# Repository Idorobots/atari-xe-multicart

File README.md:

# XE Multicart

A multi-game cartridge for the Atari 400/800/XL/XE with software game selection which can hold up to 127 games!

# How it works?

A `74HCT373` latch is used for extra address pins, it's accessed by writing to the cartridge control block (`$DF00`) causing a bank switch. After selecting appropriate ROM bank, the firmare resets the console in turn starting the game. To select another game, reboot your Atari.

# Assembly instructions
## PCB
Assuming that you already have the PCBs on hand, either by ordering them on-line or creating them yourself, the assembly is pretty simple - just solder the `74HTC373` latch, the transistor and the passive components. It is highly recommended to solder a socket for the memory chip as it makes it much easier to re-program it. **Also, keep in mind that the component side goes into the console facing down, so prepare your case accordingly.**

## Memory chip configuration

The PCB layout of this cartridge is customizable - you can fit any 28/32-pin JEDEC-compliant EPROM chip in the `27C` line or compatible flash memory chip with size ranging from as low as 64 kbit up to 8 mbit. Fitting larger chips means you will be able to store more game ROMs (up to 127 total), but you can also use this layout without the game selection firmware to store any single standard 8k/16k game you want.

### Jumper settings

There are four jumpers on the PCB - `JP1` to `JP4` - oriented vertically when looking at the top layer with the edge connector facing down:

```
      0   0   0   0\ UP
DOWN /0   0   0   0/
     \0   0   0   0
     JP1 JP2 JP3 JP4
```

These are used to configure the cartridge for the appropriate memory chip. The following table lists jumper settings for various common configurations (UP means "short top two pins", DOWN means "short bottom two pins" and X means "don't care"):

| Memory chip size | JP1  | JP2  | JP3  | JP4  |
| ---------------- | ---- | ---- | ---- | ---- |
| 64k (27C64)      | X    | X    | UP   | UP   |
| 128k (27C128)    | X    | X    | UP   | UP   |
| 256k (27C256)    | X    | X    | UP   | DOWN |
| 512k (27C512)    | X    | X    | UP   | DOWN |
| 1m (27C010)       | UP   | UP   | X    | DOWN |
| 2m (27C020)       | UP   | UP   | DOWN | DOWN |
| 4m (27C040)       | UP   | DOWN | DOWN | DOWN |
| 8m (27C080)       | DOWN | DOWN | DOWN | DOWN |

## Building the firmware
### Prerequisites
To succesfully build the firmware for the multicart, you will need to set up the following dependencies on your system:
- `make` - the Make build system,
- `python3` - Python programming language version 3.*,
- `gcc` - GNU Compiler Collection,
- `cc65`- the [CC65 compiler](https://cc65.github.io/).

### Build
In order to build the firmware & a cartridge image you will need some standard 8k/16k ROM files (obtainable freely on the Internet). Install all the dependencies, put your ROMs into the `roms/` directory and type:

```
make
```

This will run a script that automatically detects and arranges the games, builds the firmware and compiles a cartridge image ready for burning with your favourite EPROM burner.

Alternatively, you can supply a custom ROMs directory like this:

```
make ROMS=path/to/roms/directory
```

If you encounter any troubles while building, make sure to rebuild everything cleanly:

```
make clean && make
```
## Building from a docker container

In order to build the container itself run the following command in project directory

```
docker build -t atari_xe_multicart:latest .
```

After the container is ready to use run the following command to create `cart.bin` file. It assumes that .rom files are inside the /roms directory inside project directory.

```
docker run -ti --rm -v $(pwd)/roms/:/input/ -v $(pwd):/output/ atari_xe_multicart
```

# Running in an emulator

Multicart images don't work in any emulators that I know of, because they are using a custom (if simplistic) bank-switching mechanism. For testing purposes, you can run just the `menu.bin` (the game selection firmware) by loading it as a standard 8k cartridge ROM in your favourite Atari 800/XE emulator. For example:

```
atari800 -xl -xlxe_rom path/to/ATARIXL.ROM -cart menu.bin
```

It'll display the game selection menu, but any attempts at selecting a game will result in restarting the game selection menu.

# License

Software & hardware licensed under the MIT license (see LICENSE file for details). The OSHW logo comes from the [BFL library](http://www.baconfatlabs.com/2011/11/oshw-eagle-symbols-for-schematic-and-silkscreen/), licensed under CC-BY-SA. Any commercial product names seen on software screenshots are for demonstration purposes only and are not included with this product.

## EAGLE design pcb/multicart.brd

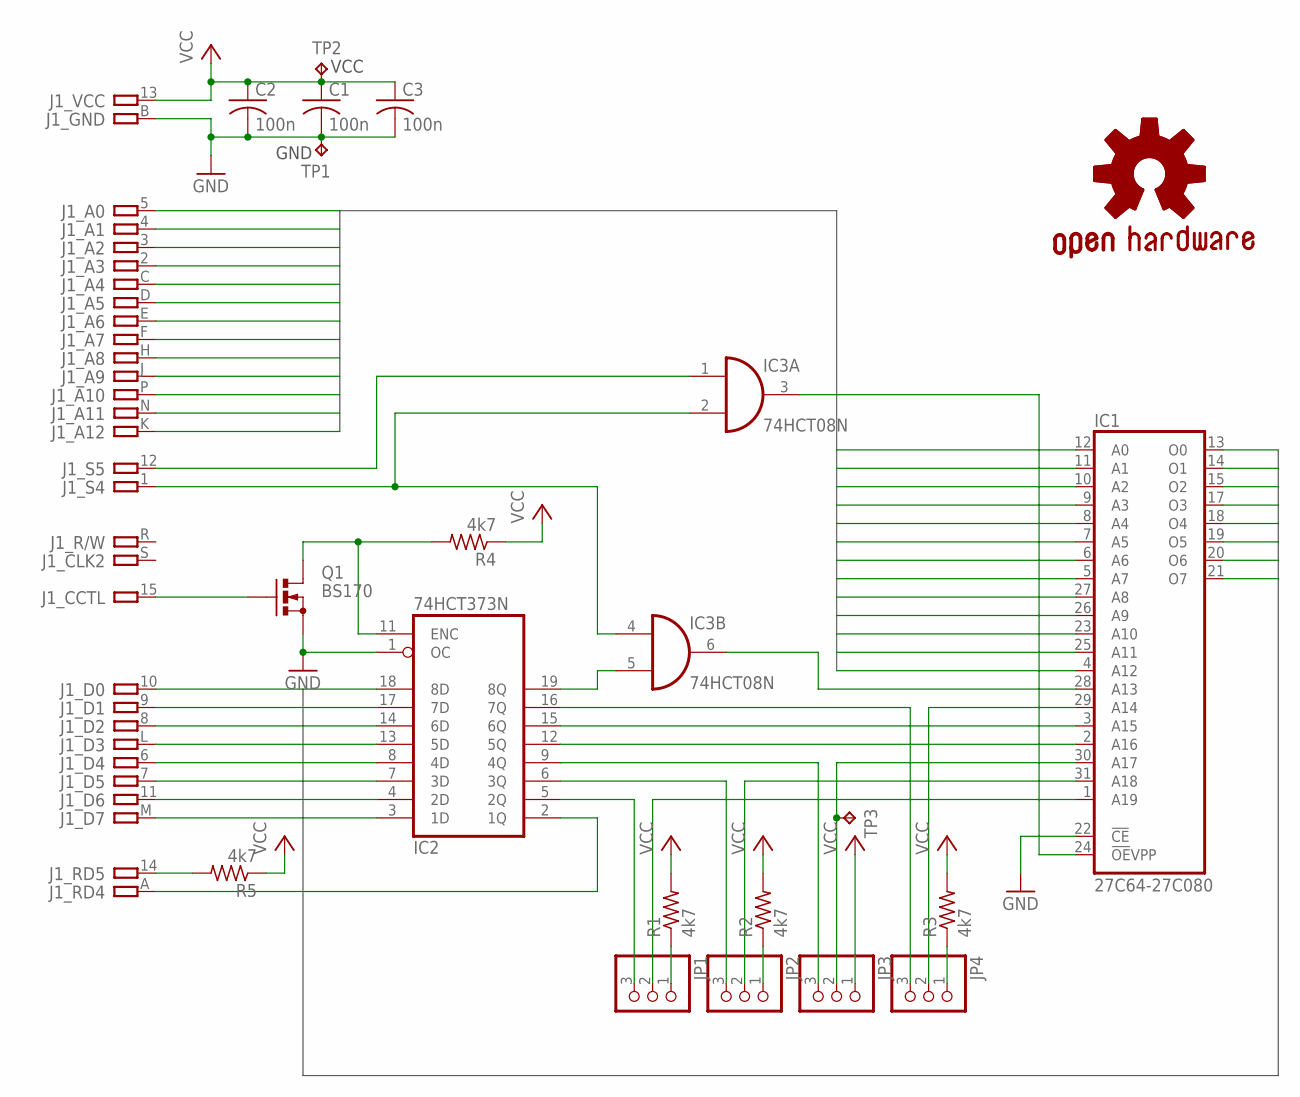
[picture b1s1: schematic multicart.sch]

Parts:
C1, C2, C3: 100n; C025-025X050
GOLD_ORB_SM1: OSHWLOGO_GOLD_ORB_SM; OSHW2
IC1: 27C64-27C080; DIL32
IC2: 74HCT373N; DIL20
IC3: 74HCT08N; DIL14
J1: ATARI-800
JP1, JP2, JP3, JP4: PINHD-1X3; 1X03
Q1: BS170; SOT54E
R1, R2, R3, R4, R5: 4k7; 0204/7
TP1, TP2, TP3: TPB1,27; B1,27

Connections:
A0: IC1.12 (A0), J1.5
A1: IC1.11 (A1), J1.4
A2: IC1.10 (A2), J1.3
A3: IC1.9 (A3), J1.2
A4: IC1.8 (A4), J1.C
A5: IC1.7 (A5), J1.D
A6: IC1.6 (A6), J1.E
A7: IC1.5 (A7), J1.F
A8: IC1.27 (A8), J1.H
A9: IC1.26 (A9), J1.J
A10: IC1.23 (A10), J1.P
A11: IC1.25 (A11), J1.N
A12: IC1.4 (A12), J1.K
D0: IC1.13 (O0), IC2.18 (8D), J1.10
D1: IC1.14 (O1), IC2.17 (7D), J1.9
D2: IC1.15 (O2), IC2.14 (6D), J1.8
D3: IC1.17 (O3), IC2.13 (5D), J1.L
D4: IC1.18 (O4), IC2.8 (4D), J1.6
D5: IC1.19 (O5), IC2.7 (3D), J1.7
D6: IC1.20 (O6), IC2.4 (2D), J1.11
D7: IC1.21 (O7), IC2.3 (1D), J1.M
GND: C1.2, C2.2, C3.2, IC1.16 (GND), IC1.22 (!CE), IC2.1 (OC), IC2.10 (GND), IC3.7 (GND), J1.B, Q1.S, TP1.TP
unnamed: IC2.19 (8Q), IC3.5 (I1)
unnamed: IC2.16 (7Q), JP4.3
unnamed: IC1.3 (A15), IC2.15 (6Q)
unnamed: IC1.2 (A16), IC2.12 (5Q)
unnamed: IC2.9 (4Q), JP3.3
unnamed: IC2.6 (3Q), JP2.3
unnamed: IC2.11 (ENC), Q1.D, R4.2
unnamed: J1.15, Q1.G
unnamed: JP1.1, R1.1
unnamed: IC1.31 (A18), JP2.2
unnamed: JP2.1, R2.1
unnamed: IC1.30 (A17), JP3.2, TP3.TP
unnamed: IC1.1 (A19), JP1.2
unnamed: IC2.5 (2Q), JP1.3
unnamed: IC1.29 (A14), JP4.2
unnamed: JP4.1, R3.1
unnamed: J1.14, R5.2
unnamed: IC3.1 (I0), J1.12
unnamed: IC3.2 (I1), IC3.4 (I0), J1.1
unnamed: IC1.28 (A13), IC3.6 (O)
unnamed: IC2.2 (1Q), J1.A
unnamed: IC1.24 (!OE!VPP), IC3.3 (O)
VCC: C1.1, C2.1, C3.1, IC1.32 (VCC), IC2.20 (VCC), IC3.14 (VCC), J1.13, JP3.1, R1.2, R2.2, R3.2, R4.1, R5.1, TP2.TP

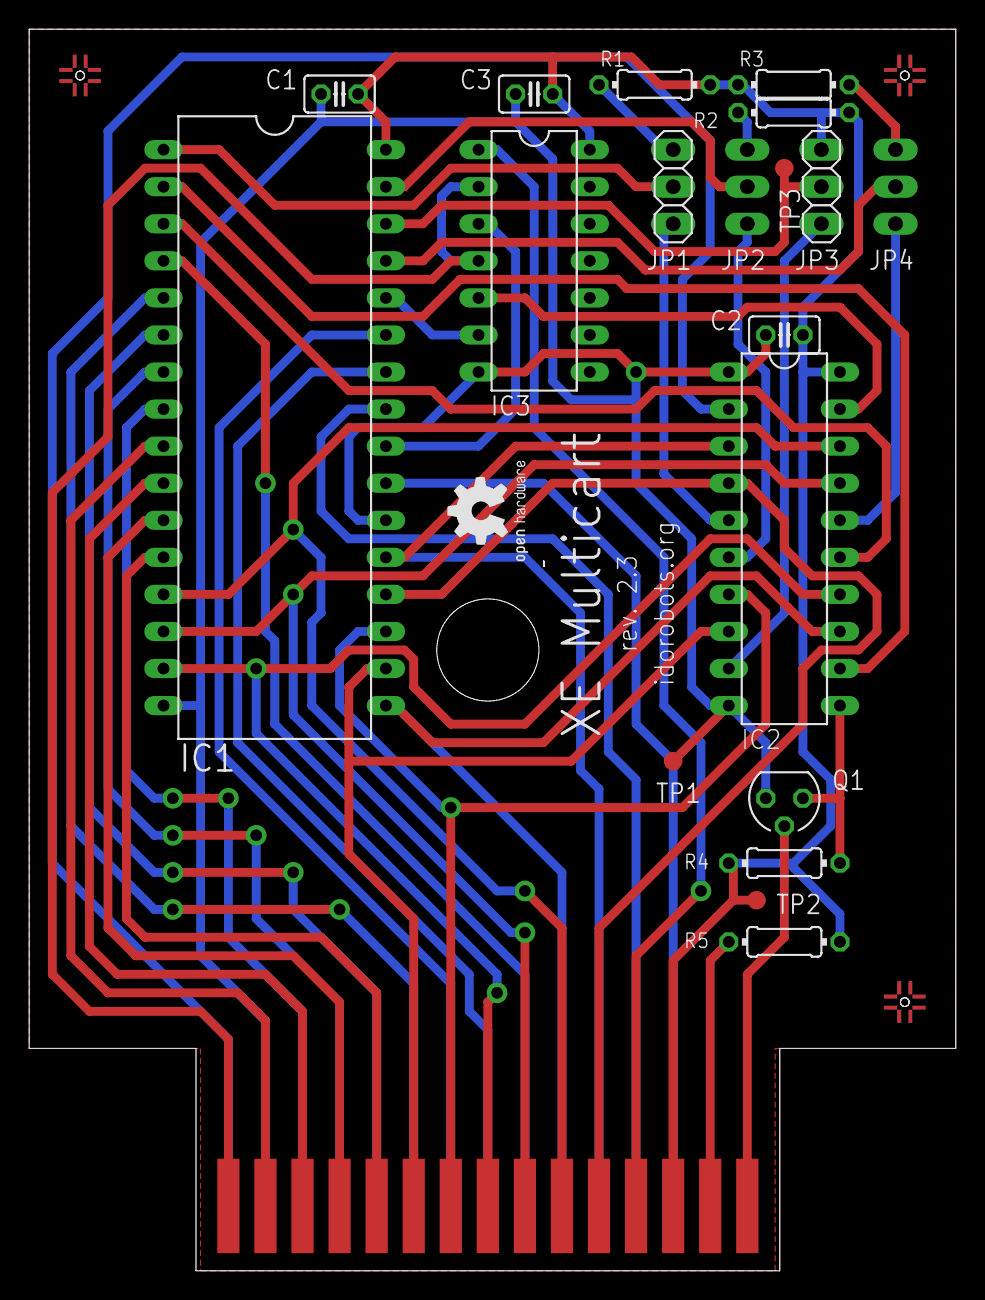
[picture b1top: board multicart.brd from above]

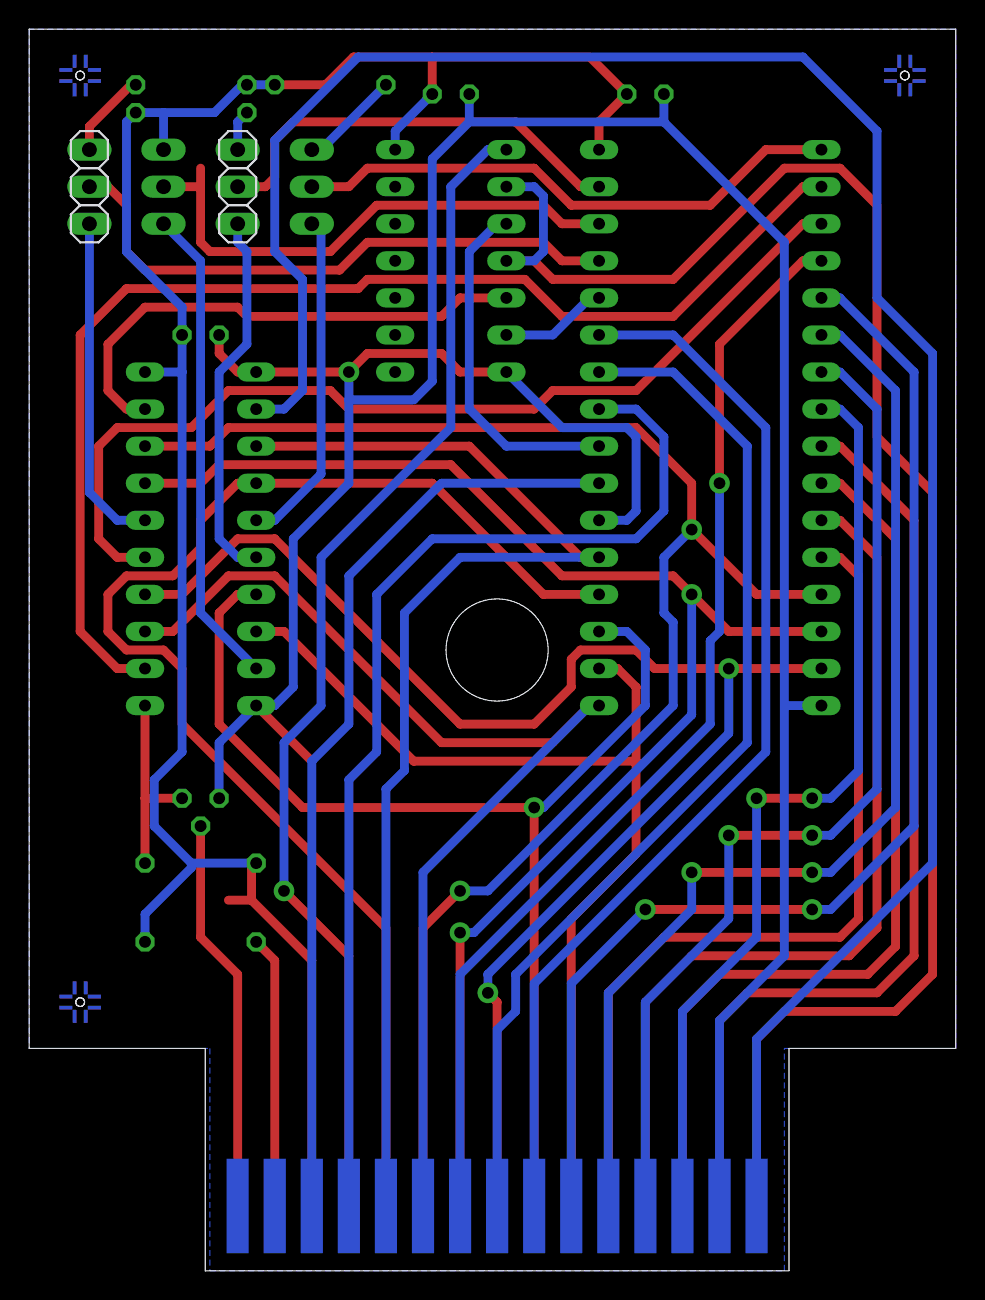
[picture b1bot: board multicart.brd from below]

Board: 2 copper layers, 63.5 x 85.1 mm, 27 parts (5 on the bottom side), 45 nets.

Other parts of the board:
U$1, U$2, U$3, U$4, U$5, U$6: PASSER-HOLE

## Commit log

2016-04-04 Added schematic of the multi-cart.
2016-04-04 Updated the README.
2016-04-04 Changed cart connector package & removed unused signals.
2016-04-04 Added PCB layout of the multicart.
2016-04-04 Added a stub of the game selection software.
2016-04-05 Swapped cart bank mapping & reorganized the PCB.
    Fixes #1
2016-04-05 Optimized the design.
2016-04-05 Added bypass caps to the design.
2016-04-06 Modified the design to support both 8k and 16k standard games.
2016-04-06 Implemented bulk of the firmware logic.
2016-04-06 Hold on... What if a game actually uses the second cart bank?
    Silly me.
2016-04-06 Ensured that the backed up code works as expected.
2016-04-06 Fixed bad C runtime teardown when swapping games.
    Fixes #4
2016-04-06 Refactored the code a little.
2016-04-07 Removed the RD5 line resistor.
2016-04-07 Optimized the design a little.
2016-04-07 Added pull-downs to the CCTL & R/W lines.
2016-04-08 Optimized the design by using AND gates.
2016-04-09 Moved some definitions into a header file.
2016-04-09 Added a better game selection menu.
2016-04-09 Moved Makefile outside of the src directory.
2016-04-09 Added a stub of cart creating script.
2016-04-09 Added cart.bin generation to the script.
2016-04-10 Improved game ordering in the selection menu.
2016-04-10 Fixed wonky if condition.
2016-04-10 Improved game selection screen.
2016-04-10 Updated the schematic to support 8-mbit flash chips.
2016-04-10 Updated the PCB design.
2016-04-10 Optimized the PCB design.
2016-04-10 Made firmware properly work with 8mbit flash.
2016-04-12 Added some sparkles to the PCB layout.
2016-04-12 Added OSHW logo to the PCB & the schematic.
2016-04-12 Updated the licensing info.
2016-04-13 Ensure that Python v3 is used when building the cart.
2016-04-14 Added test points for power.
2016-04-14 Vectorized silkscreen fonts.
2016-04-14 Turned alignment vias into full-fledged holes.
2016-04-14 Adjusted the PCB dimension for manufacture.
2016-04-14 Adjusted some traces for manufacture.
2016-04-14 Removed trademarks from the project.
2016-04-14 Updated the design to fit into a Z7 cart case.
2016-04-15 Increased the via drill size.
2016-04-15 Used proper alignment markers instead of vias.
2016-04-16 Updated multicart logo in the menu.
2016-04-16 Moved the board to match the origin.
2016-04-19 Adjusted the board dimensions to better fit into a Z7 case.
2016-04-19 Adjusted trace widths to make home etching easier.
2016-04-22 Added a prototype picture.
2016-04-23 Added input buffer clearing on bad input line.
2016-04-23 Decreased the delay after logo is displayed.
2016-04-23 Ensured that the CC65 runtime is reset properly on console reset.
2016-04-25 Added a safety resistor to the RD5 line.
    This makes it harder to break stuff when the cart is inserted upside
    down.
2018-02-06 Made buildcart.py treat "bad" ROM files in a nicer way.
2018-02-06 Added a placeholder README to the roms/ directory, to make it more clear where to put the ROM files.
2018-02-06 Made sure that the menu file is generated as the first thing.
2018-02-06 Updated the linker config for the latest cc65.
2018-02-06 Refactored games.c creation to produce full, compilable C source file.
2018-02-06 Added generated files to the .gitignore.
2018-02-06 Added customized ROMs directory to the README.
2018-02-06 Added a helpful message when no viable ROMs are present.
2018-02-06 Added a section on emulators to the README.
2018-07-26 Made explicit notion of the PCB orientation when inserting the cart into the console.
2022-07-04 Updated the README
2022-07-04 Updated the README with yet more information.
2022-07-04 Fixed a type in README
2022-09-17 Docker container and build command
2022-09-17 Latest ubuntu image and better apt usage
2022-09-17 Removed the cart.bin file
2022-09-17 Removed unnecesary package definition for cc65
